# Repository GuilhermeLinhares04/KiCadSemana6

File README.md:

# KiCadSemana6

O repositório contém arquivos relacionados a um projeto de circuito impresso (PCB). Aqui está uma descrição dos arquivos e diretórios presentes:

- `pon_sem_6-backups`: Este diretório contém backups ou versões anteriores dos arquivos do projeto.
- `fp-info-cache`: Diretório utilizado para armazenar informações em cache relacionadas aos footprints (marcas de componentes) utilizados no projeto.
- `Arquivos com extensão .gbr`: Estes são arquivos Gerber, que descrevem as camadas do PCB para a fabricação. As diferentes extensões indicam camadas específicas, como camada superior (F_Cu), camada inferior (B_Cu), máscara de solda (F_Mask e B_Mask), pasta de solda (F_Paste e B_Paste), e serigrafia (F_Silkscreen e B_Silkscreen).
- `pon_sem_6-Edge_Cuts.gbr`: Arquivo Gerber que descreve os cortes da placa, ou seja, as bordas externas da placa.
- `Arquivos com extensão .drl`: Estes são arquivos de perfuração, descrevendo as localizações dos furos nas camadas do PCB. pon_sem_6-NPTH.drl pode conter informações sobre furos não metalizados (non-plated through holes), enquanto pon_sem_6-PTH.drl pode conter informações sobre furos metalizados (plated through holes).
- `pon_sem_6-job.gbrjob`: Arquivo de configuração ou trabalho para o processo de fabricação do PCB.
- `pon_sem_6.kicad_pcb`: Arquivo principal do projeto PCB.
- `pon_sem_6.kicad_prl`: Arquivo de lista de regras (rules) para o projeto no KiCad.
- `pon_sem_6.kicad_pro`: Arquivo de projeto do KiCad contendo informações sobre as configurações e preferências do projeto.
- `pon_sem_6.kicad_sch`: Arquivo de esquemático do KiCad, descrevendo o esquema elétrico do projeto.
- `report.txt`: Arquivo de relatório dos arquivos Gerber do projeto.

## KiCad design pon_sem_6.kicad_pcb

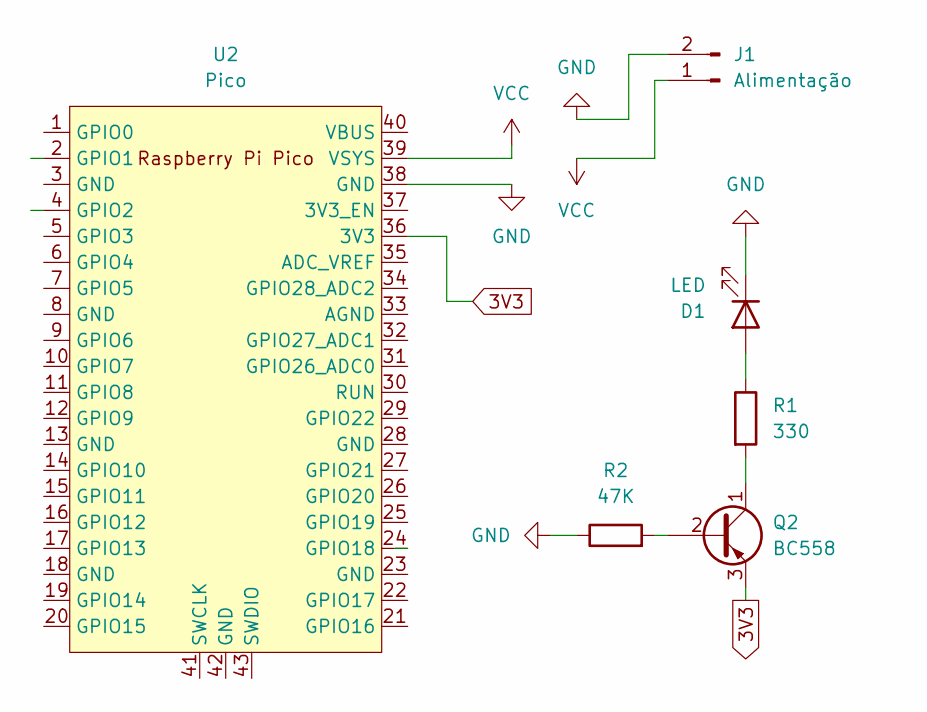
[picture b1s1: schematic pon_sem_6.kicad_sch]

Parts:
D1: LED; LED_D1.8mm_W1.8mm_H2.4mm_Horizontal_O3.81mm_Z1.6mm
J1: Alimentação; Hirose_DF13-02P-1.25DSA_1x02_P1.25mm_Vertical
Q2: BC558; TO-92_Inline
R1: 330; R_1206_3216Metric_Pad1.30x1.75mm_HandSolder
R2: 47K; R_1206_3216Metric_Pad1.30x1.75mm_HandSolder
U2: Pico; RPi_Pico_SMD_TH

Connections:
3V3: Q2.3 (E), U2.36 (3V3)
GND: D1.1 (K), J1.2, R2.1, U2.38 (GND)
unnamed: D1.2 (A), R1.1
unnamed: Q2.2 (B), R2.2
unnamed: Q2.1 (C), R1.2
VCC: J1.1, U2.39 (VSYS)

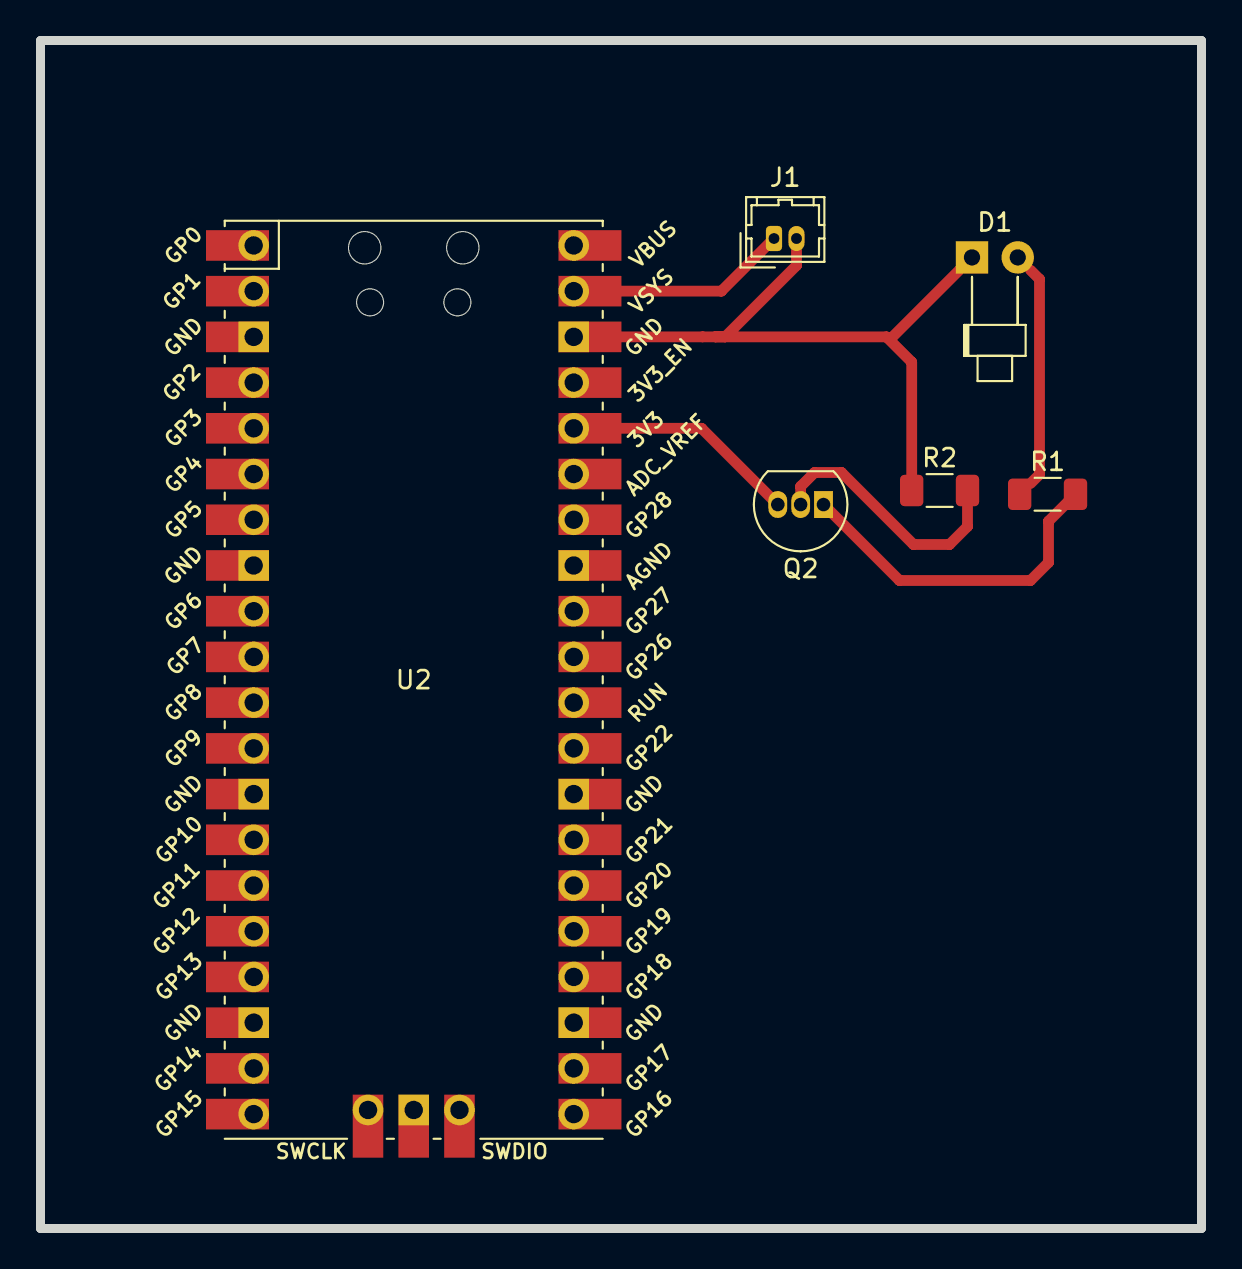
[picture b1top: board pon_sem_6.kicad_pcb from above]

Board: 2 copper layers, 64.5 x 66.0 mm, 6 parts (0 on the bottom side), 6 nets.

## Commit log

2024-03-28 Adição de arquivos
